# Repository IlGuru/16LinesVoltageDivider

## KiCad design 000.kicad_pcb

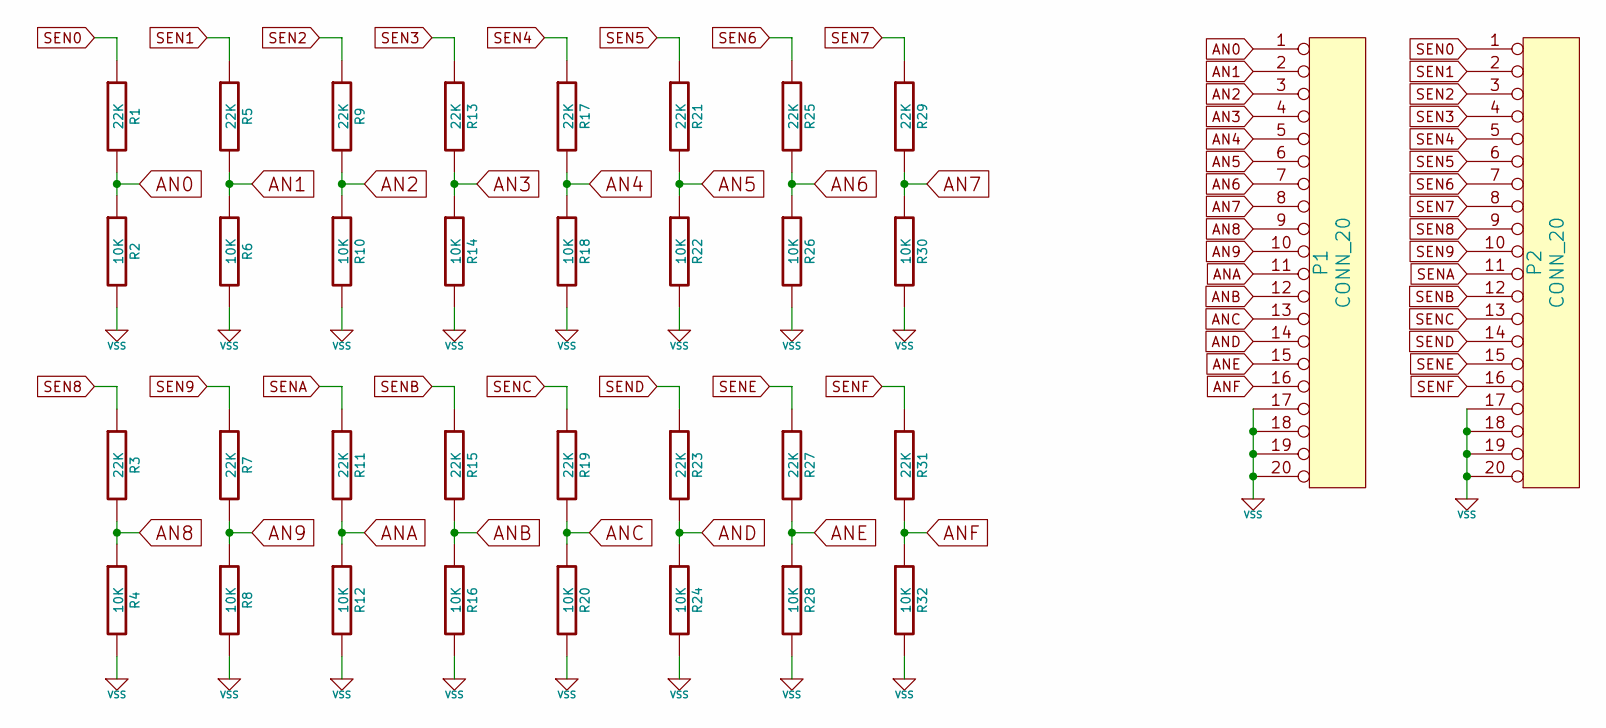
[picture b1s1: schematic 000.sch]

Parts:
P1, P2: CONN_20
R1, R3, R5, R7, R9, R11, R13, R15, R17, R19, R21, R23, R25, R27, R29, R31: 22K
R2, R4, R6, R8, R10, R12, R14, R16, R18, R20, R22, R24, R26, R28, R30, R32: 10K

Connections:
AN0: P1.1, R1.2, R2.1
AN1: P1.2, R5.2, R6.1
AN2: P1.3, R9.2, R10.1
AN3: P1.4, R13.2, R14.1
AN4: P1.5, R17.2, R18.1
AN5: P1.6, R21.2, R22.1
AN6: P1.7, R25.2, R26.1
AN7: P1.8, R29.2, R30.1
AN8: P1.9, R3.2, R4.1
AN9: P1.10, R7.2, R8.1
ANA: P1.11, R11.2, R12.1
ANB: P1.12, R15.2, R16.1
ANC: P1.13, R19.2, R20.1
AND: P1.14, R23.2, R24.1
ANE: P1.15, R27.2, R28.1
ANF: P1.16, R31.2, R32.1
SEN0: P2.1, R1.1
SEN1: P2.2, R5.1
SEN2: P2.3, R9.1
SEN3: P2.4, R13.1
SEN4: P2.5, R17.1
SEN5: P2.6, R21.1
SEN6: P2.7, R25.1
SEN7: P2.8, R29.1
SEN8: P2.9, R3.1
SEN9: P2.10, R7.1
SENA: P2.11, R11.1
SENB: P2.12, R15.1
SENC: P2.13, R19.1
SEND: P2.14, R23.1
SENE: P2.15, R27.1
SENF: P2.16, R31.1
VSS: P1.17, P1.18, P1.19, P1.20, P2.17, P2.18, P2.19, P2.20, R2.2, R4.2, R6.2, R8.2, R10.2, R12.2, R14.2, R16.2, R18.2, R20.2, R22.2, R24.2, R26.2, R28.2, R30.2, R32.2

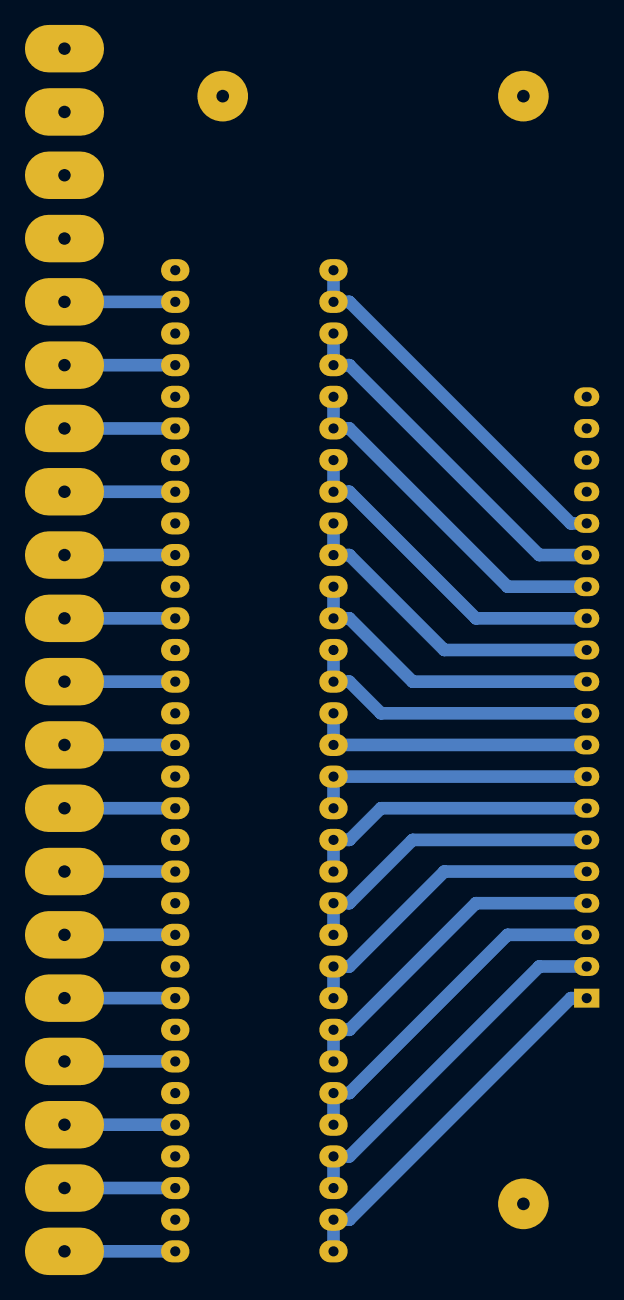
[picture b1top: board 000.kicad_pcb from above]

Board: 2 copper layers, 37 parts (0 on the bottom side), 33 nets.

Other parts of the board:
1PIN, 1PIN#2, 1PIN#3: P***; 1pin

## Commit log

2015-09-21 Versione per kicad 3
